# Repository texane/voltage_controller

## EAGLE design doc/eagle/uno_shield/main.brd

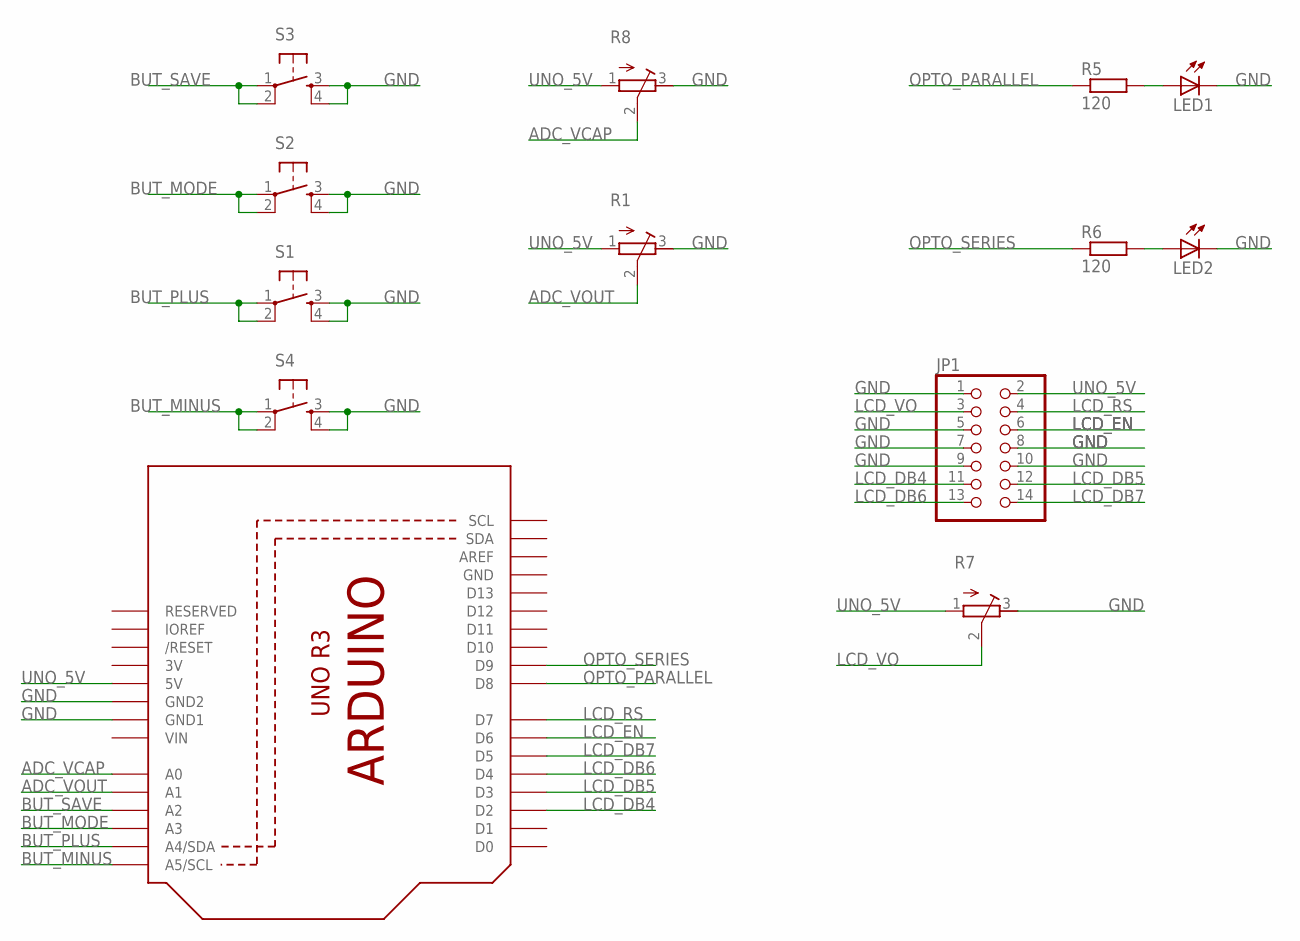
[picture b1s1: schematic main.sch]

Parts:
JP1: PINHD-2X7; 2X07
LED1, LED2: LED5MM
R1, R7, R8: R-TRIMM3339P; RTRIM3339P
R5, R6: 120; 0204/5
S1, S2, S3, S4: TAC_SWITCHPTH; TACTILE-PTH
U1: ARDUINOR3-BPLACE

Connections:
3V: U1.3V
ADC_VCAP: R8.2 (S), U1.A0
ADC_VOUT: R1.2 (S), U1.A1
BUT_MINUS: S4.1, S4.2, U1.A5 (A5/SCL)
BUT_MODE: S2.1, S2.2, U1.A3
BUT_PLUS: S1.1, S1.2, U1.A4 (A4/SDA)
BUT_SAVE: S3.1, S3.2, U1.A2
GND: JP1.1, JP1.5, JP1.7, JP1.8, JP1.9, JP1.10, LED1.K (C), LED2.K (C), R1.3 (A), R7.3 (A), R8.3 (A), S1.3, S1.4, S2.3, S2.4, S3.3, S3.4, S4.3, S4.4, U1.GND, U1.GND1, U1.GND2
LCD_DB4: JP1.11, U1.D2
LCD_DB5: JP1.12, U1.D3
LCD_DB6: JP1.13, U1.D4
LCD_DB7: JP1.14, U1.D5
LCD_EN: JP1.6, U1.D6
LCD_RS: JP1.4, U1.D7
LCD_VO: JP1.3, R7.2 (S)
unnamed: LED1.A, R5.2
unnamed: LED2.A, R6.2
OPTO_PARALLEL: R5.1, U1.D8
OPTO_SERIES: R6.1, U1.D9
UNO_5V: JP1.2, R1.1 (E), R7.1 (E), R8.1 (E), U1.5V
VIN: U1.VIN

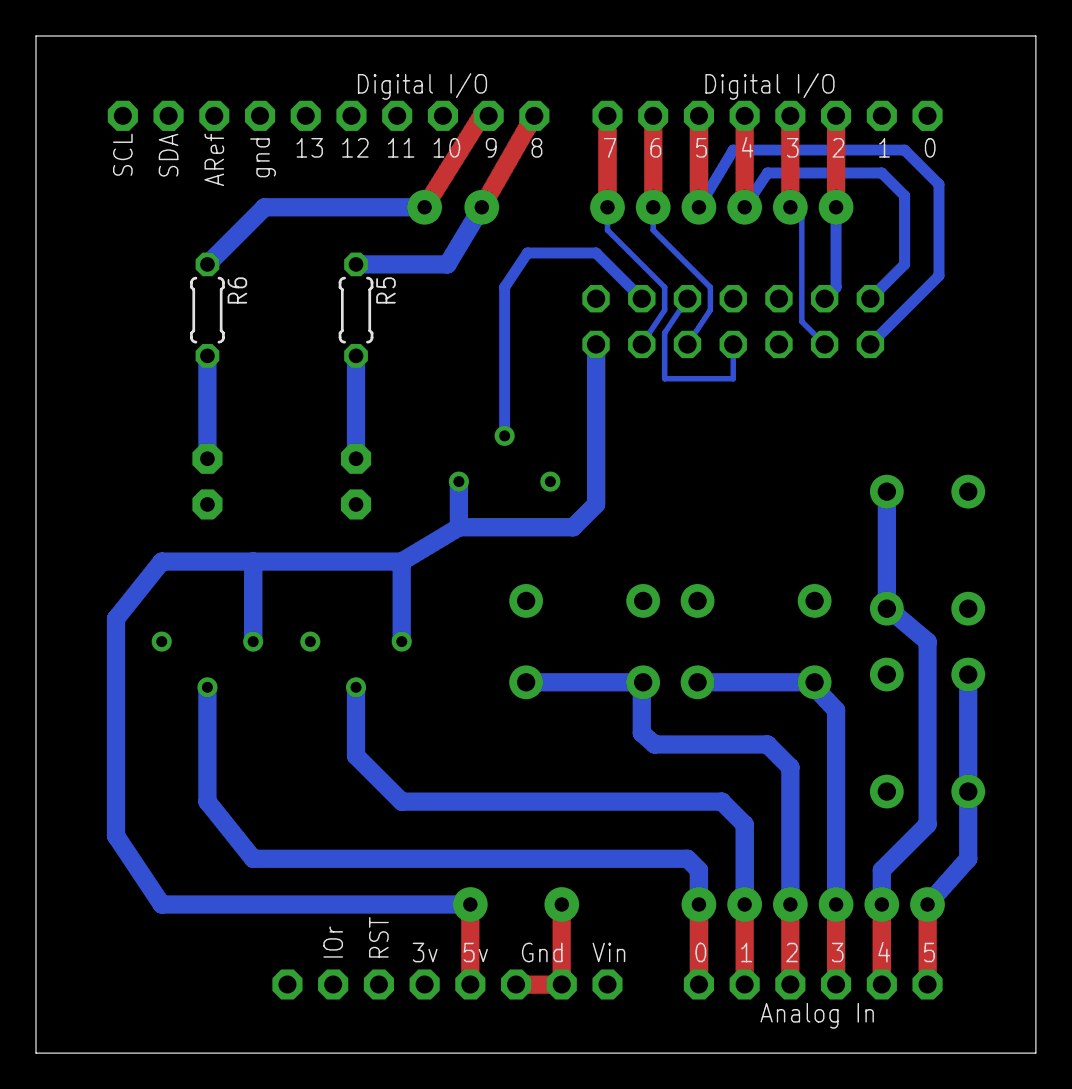
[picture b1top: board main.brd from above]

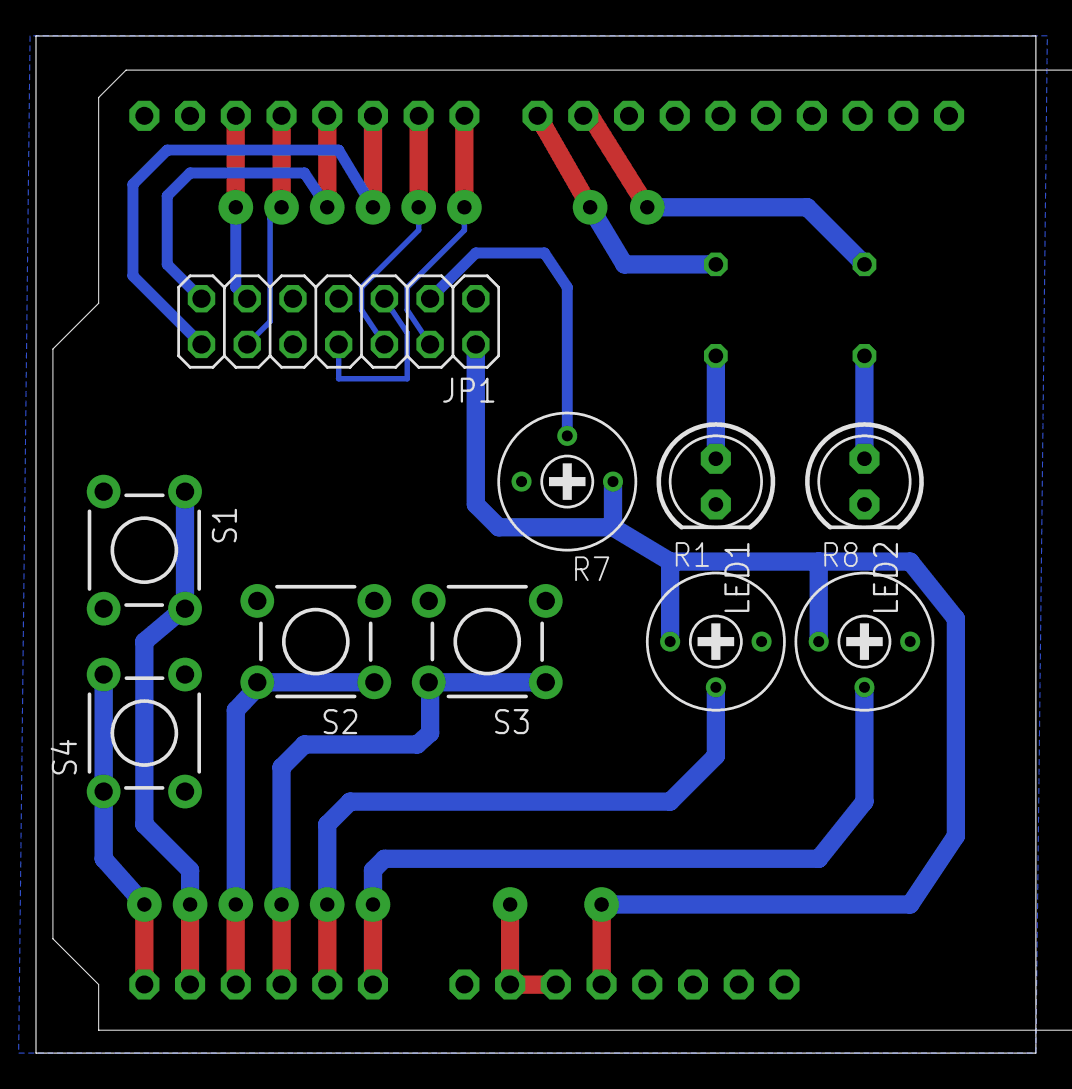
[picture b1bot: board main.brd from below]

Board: 2 copper layers, 55.5 x 56.5 mm, 13 parts (10 on the bottom side), 19 nets.

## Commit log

2013-05-18 [ add ] src
2013-05-18 [ update ] main.c comments on operating theory and conditions
2013-05-19 [ update ] main, wip
2013-05-19 [ update ] main, EEPROM comment mistake
2013-05-19 [ update ] use libavr EEPROM routines
2013-05-19 [ add ] doc/dia/io
2013-05-19 [ add ] upload.sh
2013-05-19 [ update ] button handling
2013-05-19 [ update ] opto control pins
2013-05-19 [ update ] adc
2013-05-19 [ add ] eagle/uno_shield
2013-05-19 [ fix ] dia/io pins
2013-05-20 [ add ] routed board, main.png
2013-05-20 [ fix ] uno_shield board
2013-05-20 [ update, fix ] add debugging. check conf value range. buttons pressed low.
2013-05-20 [ fix ] use LCD_POS_DB
2013-05-20 [ update ] lcd_goto_xy
2013-05-20 [ update ] lcd_goto_xy optim
2013-05-20 [ update ] adc, single conversion mode
2013-05-20 [ update ] dummy ppm
2013-05-21 [ update ] button handling logic
2013-05-21 [ update ] ticks_to_ms_string
2013-05-21 [ update ] scaled_volts_to_string
2013-05-21 [ add ] doc/ui
2013-05-22 [ add ] main.hex
2013-05-22 [ update ] ui notes
2013-05-23 [ add ] eagle/voltage_scaling_stage
2013-05-23 [ update ] eagle/voltage_scaling_stage
2013-05-23 [ add ] main/main.ino
2013-05-23 [ update ] voltage_scaling_stage
2013-05-23 [ add ] voltage_scaling_stage/notes
2013-05-23 [ add ] voltage_scaling_stage/main.png

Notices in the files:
parts and their libraries:
SparkFun-Electromechanical: Licensing: CC v3.0 Share-Alike You are welcome to use this library for commercial purposes.
